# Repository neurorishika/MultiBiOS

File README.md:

# MultiBiOS: Precision Olfactometer Control System

<div align="center">

**High-precision, hardware-clocked olfactometer control system for behavioral neuroscience**

[📚 Documentation](https://neurorishika.github.io/MultiBiOS/) • [🚀 Quick Start](#quick-start) • [🔧 Installation](#installation) • [📖 Examples](#examples) • [🤝 Contributing](#contributing)

</div>

---

## 🧪 Overview

**MultiBiOS** (Multispecies Bilateral Odor delivery System) is a precision olfactometer control system designed for behavioral neuroscience experiments. It provides sub-millisecond timing control, complete experimental reproducibility, and comprehensive data logging.

### ✨ Key Features

- 🎯 **Sub-millisecond precision** with hardware-clocked timing via NI-DAQ
- 🔄 **Bilateral valve control** for complex comparative experiments  
- 📊 **Complete data provenance** with comprehensive logging and replay
- 🛡️ **Built-in safety guardrails** prevent timing conflicts at compile-time
- 🎲 **Reproducible randomization** via configurable random seeds
- 📈 **Interactive visualization** with real-time and post-hoc analysis
- ⏱️ **Real-time progress monitoring** shows expected protocol state during execution
- 🔌 **Teensy 4.1 firmware** for microsecond-precise valve preloading
- 📝 **YAML protocols** for human-readable experimental descriptions

### 🏗️ System Architecture

```
┌─────────────────┐    ┌─────────────────┐    ┌─────────────────┐
│   YAML Protocol │───▶│ Python Compiler │───▶│   NI-DAQ USB    │
│   Description   │    │   & Runner      │    │    6353         │
└─────────────────┘    └─────────────────┘    └─────────────────┘
                                                        │
                                                        ▼
                              ┌─────────────────────────────────────┐
                              │          Teensy 4.1 MCU             │
                              │    (Valve Pattern Preloading)      │
                              └─────────────────────────────────────┘
                                                │
                                                ▼
                              ┌─────────────────────────────────────┐
                              │       TPIC6B595 Shift Registers    │
                              │         (10MHz SPI Chain)          │
                              └─────────────────────────────────────┘
                                                │
                                                ▼
                              ┌─────────────────────────────────────┐
                              │      Olfactometer Valve Arrays     │
                              │    (8-valve bilateral control)     │
                              └─────────────────────────────────────┘
```

## 🚀 Quick Start

### Prerequisites

- Conda or Miniconda
- NI-DAQmx drivers (for hardware execution)
- Spinnaker SDK 4.3.0.189 installed on Windows before installing `PySpin`
- If you want live Blackfly input in FicTrac on this rig, build a Spinnaker-enabled FicTrac binary and configure the `fictrac` block in `config/hardware.yaml`

### Installation

```bash
# Clone the repository
git clone https://github.com/neurorishika/MultiBiOS.git
cd MultiBiOS

# Create the shared NI-DAQ + Blackfly camera environment
conda env create -f environment.yml
conda activate multibios-blackfly

# Verify the combined stack
python -c "import multibios, nidaqmx, PySpin; print('multibios-blackfly ready')"

# Optional app smoke tests
multibios-explorer --help
multibios-flow-monitor --help
```

This environment is intended to run both the MultiBiOS DAQ stack and the Blackfly camera scripts in one place. The rig camera model is **Teledyne FLIR Blackfly S BFS-U3-13Y3M**.

For live FicTrac on the Blackfly side camera, see `docs/fictrac.md`. MultiBiOS now prepares the Spinnaker runtime DLL path automatically before launching FicTrac, but you still need a FicTrac binary built with the upstream `PGR_USB3` option.

If you are on this workstation and want the same validated build that was used for the Blackfly side camera, run:

```powershell
cd C:\Rishika\MultiBiOS
.\tools\build_fictrac_spinnaker.ps1 -VcpkgRoot C:\Users\markd\vcpkg
```

The resulting binary is expected at `assets/fictrac-spinnaker/fictrac-spinnaker.exe`. The step-by-step build and usage guide lives in `docs/fictrac.md`.

FicTrac is treated as vendored source in this repo because MultiBiOS carries source-level patches in `assets/third_party/FicTrac`. The local build directory `assets/third_party/FicTrac-build` should remain untracked.

### Your First Protocol

1. **Preview a protocol** (no hardware required):
   ```bash
     python -m multibios.run_protocol \
      --yaml protocols/example_protocol.yaml \
       --hardware config/hardware.yaml \
       --dry-run --interactive
   ```

2. **Run on hardware** (requires NI-DAQ setup):
   ```bash
     python -m multibios.run_protocol \
      --yaml protocols/example_protocol.yaml \
       --hardware config/hardware.yaml
   ```

3. **Run with real-time progress monitoring**:
   ```bash
     python -m multibios.run_protocol \
      --yaml protocols/example_protocol.yaml \
       --hardware config/hardware.yaml \
       --verbose --progress
   ```
   
   This displays the expected protocol state during execution:
   ```
   DO Legend: [0:RCK] [1:LOAD_REQ] [2:S0] [3:S1] [4:S2]
   AO Legend: [0:MFC1] [1:MFC2]
   [  5%] 250.0ms | DO:░█░░█ | AO:0:2.50,1:1.20
   [ 10%] 500.0ms | DO:█░█░░ | AO:0:3.00,1:1.50
   ```
   (█=HIGH, ░=LOW, shows all channels at once!)

4. **Analyze results**:
   ```bash
  python -m multibios.viz_protocol data/runs/latest
   ```

## 📖 Examples

### Simple Bilateral Odor Delivery

```yaml
protocol:
  name: "Bilateral Odor Comparison"
  timing:
    sample_rate: 1000  # 1 kHz sampling
    seed: 42          # Reproducible randomization

sequence:
  - phase: "Baseline"
    duration: 30000   # 30 seconds
    times: 1
    actions:
      - device: "olfactometer.left"
        state: "AIR"
        timing: 0
      - device: "olfactometer.right"
        state: "AIR"
        timing: 0

  - phase: "Odor Presentation" 
    duration: 60000   # 1 minute per trial
    times: 5          # 5 trials
    randomize: true   # Randomize odor order
    actions:
      - device: "olfactometer.left"
        state: "ODOR1,ODOR2,ODOR3"  # Random selection
        timing: 10000               # 10s into trial
      - device: "triggers.microscope"
        state: true
        timing: 15000               # Trigger at 15s
```

### Advanced Multi-Device Coordination

```yaml
sequence:
  - phase: "Complex Trial"
    duration: 45000
    times: 10
    actions:
      # MFC setpoints
      - device: "mfc.air_left_setpoint"
        value: 2.1  # Volts
        timing: 0
      
      # Synchronized valve switching  
      - device: "olfactometer.left"
        state: "ODOR1"
        timing: 5000
      - device: "switch_valve.left"
        state: "ODOR" 
        timing: 5100  # 100ms later
        
      # Continuous camera triggers
      - device: "triggers.camera_continuous"
        state: true
        timing: 1000
      - device: "triggers.camera_continuous" 
        state: false
        timing: 40000
```

## 🔧 Hardware Setup

### Required Components

| Component | Description | Quantity |
|-----------|-------------|----------|
| **NI USB-6353** | Hardware-clocked DAQ | 1 |
| **Teensy 4.1** | Microcontroller for valve control | 1 |
| **TPIC6B595** | High-power shift registers | 4 |
| **Olfactometer valves** | Pneumatic valves (12V) | 8-16 |
| **Mass flow controllers** | Precision flow control | 2-4 |

### Wiring Overview

```
NI-DAQ ────┐
           ├─── LOAD_REQ (Hardware clock)
           ├─── S-bits (Device selection) 
           ├─── Analog I/O (MFC control)
           └─── Triggers (Microscope/Camera)

Teensy ────┐
           ├─── SPI Chain (10MHz)
           ├─── Interrupt handling
           └─── Safety interlocks

TPIC6B595 ─┼─── Valve Array Left
           ├─── Valve Array Right  
           ├─── Switch Valve Left
           └─── Switch Valve Right
```

📋 **[Complete wiring diagrams and setup instructions →](https://neurorishika.github.io/MultiBiOS/hardware/)**

## 📊 Data Output

MultiBiOS provides comprehensive data logging:

### Generated Files
```
data/runs/2025-08-21_14-07-33/
├── protocol_original.yaml      # Original protocol
├── protocol_compiled.yaml      # Compiled with timing  
├── hardware_config.yaml        # Hardware configuration
├── digital_output.npy          # DO timing arrays
├── analog_output.npy           # AO setpoints
├── analog_input.csv            # MFC feedback (if recorded)
├── timing_log.csv              # Execution timestamps
└── visualization.html          # Interactive plot
```

### Interactive Visualization

The system generates rich interactive plots showing:
- 📈 Commanded vs actual valve states
- 🎛️ Analog input/output traces  
- ⏱️ Timing precision analysis
- 🔍 Zoom and pan capabilities

## 🧪 Use Cases

MultiBiOS is designed for:

- **Behavioral choice experiments** with precise odor timing
- **Optogenetics** with synchronized light/odor delivery
- **Calcium imaging** with triggered acquisition
- **Electrophysiology** with sub-millisecond precision
- **Multi-animal** comparative studies
- **Reproducible protocols** across labs and sessions

## 🛡️ Safety & Reliability

### Built-in Safeguards
- ✅ **Compile-time validation** prevents hardware conflicts
- ✅ **Timing guardrails** ensure safe valve switching
- ✅ **State verification** with sticky S-bit monitoring  
- ✅ **Hardware interlocks** prevent damage
- ✅ **Complete logging** for audit trails

### Experimental Reproducibility
- 🎯 **Deterministic randomization** with configurable seeds
- 📝 **Complete parameter logging** 
- 🔄 **Protocol replay** capability
- 📊 **Timing validation** and verification
- 🏷️ **Version tracking** of all components

## 📚 Documentation

Comprehensive documentation is available at **[neurorishika.github.io/MultiBiOS](https://neurorishika.github.io/MultiBiOS/)**

### Quick Links
- 🏗️ [System Architecture](https://neurorishika.github.io/MultiBiOS/hardware/)
- 🔌 [Hardware Setup](https://neurorishika.github.io/MultiBiOS/wiring/) 
- 💾 [Firmware Guide](https://neurorishika.github.io/MultiBiOS/firmware/)
- 📝 [Protocol Reference](https://neurorishika.github.io/MultiBiOS/protocol/)
- 🏃 [Runner Application](https://neurorishika.github.io/MultiBiOS/runner/)
- 📈 [Visualization](https://neurorishika.github.io/MultiBiOS/visualization/)
- ❓ [FAQ](https://neurorishika.github.io/MultiBiOS/faq/)
- 🔧 [Troubleshooting](https://neurorishika.github.io/MultiBiOS/troubleshooting/)

## 🤝 Contributing

We welcome contributions! MultiBiOS is built for the neuroscience community.

### Ways to Contribute
- 🐛 **Report bugs** and request features
- 💡 **Submit improvements** to code or documentation  
- 🧪 **Share protocols** and use cases
- 🔧 **Hardware modifications** and extensions
- 📚 **Documentation** improvements

### Getting Started
```bash
# Fork the repository on GitHub
git clone https://github.com/yourusername/MultiBiOS.git
cd MultiBiOS

# Install development dependencies
poetry install --with dev

# Run tests
poetry run pytest

# Format code
poetry run black multibios/
poetry run ruff check multibios/
```

### Test And Tool Layout

- `tests/` is reserved for automated `pytest` coverage.
- `tools/manual_checks/` is for operator-facing hardware checks, probes, and bench scripts that are meant to be run directly.
- When adding new validation code, put reusable automated assertions under `tests/` and keep live camera, DAQ, MFC, or FicTrac helpers under `tools/manual_checks/`.

For a quick automated smoke pass from the repo root, run:

```bash
pytest tests/
```

📖 **[Full contributing guide →](https://neurorishika.github.io/MultiBiOS/contributing/)**

## 📄 License

This project is licensed under the MIT License - see the [LICENSE](LICENSE) file for details.

## 🙏 Acknowledgments

MultiBiOS was developed for the neuroscience research community. Special thanks to:
- The **Ruta and Kronauer Labs** for requirements and testing
- **National Instruments** for DAQ hardware support  
- The **Arduino/Teensy** community for firmware foundations
- **Open source contributors** who make science better

## 📞 Contact

- **Issues & Support:** [GitHub Issues](https://github.com/neurorishika/MultiBiOS/issues)
- **Email:** neurorishika@gmail.com  
- **Documentation:** [neurorishika.github.io/MultiBiOS](https://neurorishika.github.io/MultiBiOS/)

---

<div align="center">

**🧠 Built for Neuroscience • 🔬 Made with Science • 🚀 Open Source**

[⭐ Star this repo](https://github.com/neurorishika/MultiBiOS/stargazers) • [📖 Read the docs](https://neurorishika.github.io/MultiBiOS/) • [🤝 Contribute](CONTRIBUTING.md)

</div>

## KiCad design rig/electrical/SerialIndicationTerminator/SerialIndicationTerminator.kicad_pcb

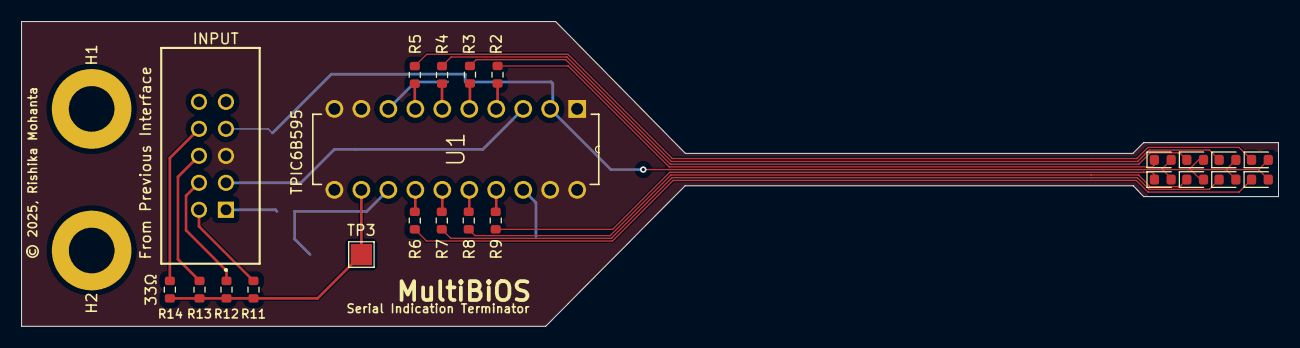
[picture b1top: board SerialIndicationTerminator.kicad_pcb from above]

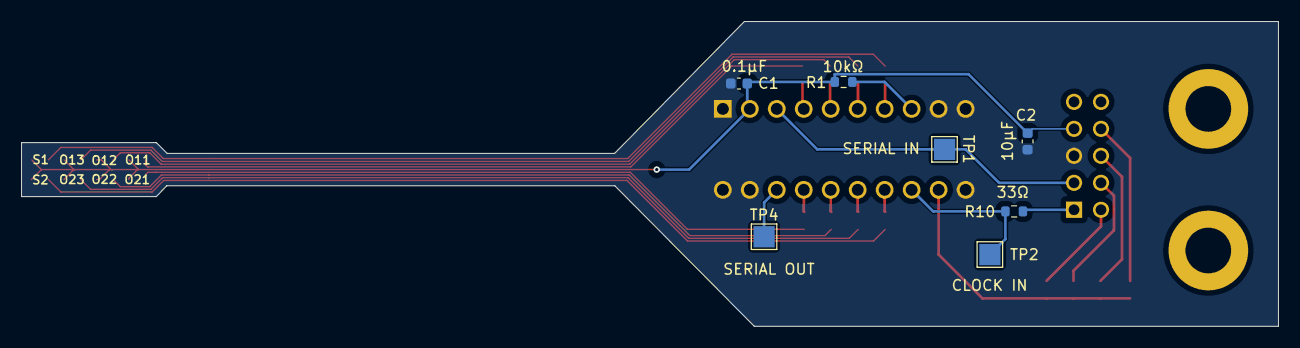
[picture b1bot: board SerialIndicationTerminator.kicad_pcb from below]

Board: 2 copper layers, 118.4 x 28.7 mm, 32 parts (7 on the bottom side), 28 nets.

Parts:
C1: 0.1u; C_0603_1608Metric
C2: 10uf; C_0603_1608Metric
D1, D2, D3, D4, D5, D6, D7, D8: LED; LED_0603_1608Metric
H1, H2: MountingHole; MountingHole_4.3mm_M4_DIN965_Pad
J1: TST-105-01-X-D; SAMTEC_TST-105-01-X-D
R1: 10k; R_0603_1608Metric
R2, R3, R4, R5, R6, R7, R8, R9: R; R_0603_1608Metric
R10, R11, R12, R13, R14: 33Ω; R_0603_1608Metric
TP1, TP2, TP3, TP4: TestPoint; TestPoint_Pad_2.0x2.0mm
U1: TPIC6595; DIP254P762X508-20

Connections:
+5V: C1.1, C2.1, D1.2 (A), D2.2 (A), D3.2 (A), D4.2 (A), D5.2 (A), D6.2 (A), D7.2 (A), D8.2 (A), J1.07, R1.2, U1.2 (VCC)
GND: C1.2, C2.2, J1.05, U1.1 (PGND), U1.9 (~G), U1.10 (PGND), U1.11 (PGND), U1.19 (LGND), U1.20 (PGND)
unnamed: D1.1 (K), R2.2
unnamed: D2.1 (K), R3.2
unnamed: D3.1 (K), R4.2
unnamed: D4.1 (K), R5.2
unnamed: D5.1 (K), R6.2
unnamed: D6.1 (K), R7.2
unnamed: D7.1 (K), R8.2
unnamed: D8.1 (K), R9.2
unnamed: J1.01, R10.1
unnamed: J1.02, R11.1
unnamed: J1.04, R12.1
unnamed: J1.06, R13.1
unnamed: J1.08, R14.1
unnamed: R2.1, U1.4 (DRAIN0)
unnamed: R3.1, U1.5 (DRAIN1)
unnamed: R4.1, U1.6 (DRAIN2)
unnamed: R5.1, U1.7 (DRAIN3)
unnamed: R6.1, U1.14 (DRAIN4)
unnamed: R7.1, U1.15 (DRAIN5)
unnamed: R8.1, U1.16 (DRAIN6)
unnamed: R9.1, U1.17 (DRAIN7)
unnamed: R11.2, R12.2, R13.2, R14.2, TP3.1, U1.12 (RCLK)
unnamed: J1.03, TP1.1, U1.3 (SER_IN)
unnamed: TP4.1, U1.18 (SER_OUT)
unnamed: R10.2, TP2.1, U1.13 (SRCK)
unnamed: R1.1, U1.8 (~SRCLR)

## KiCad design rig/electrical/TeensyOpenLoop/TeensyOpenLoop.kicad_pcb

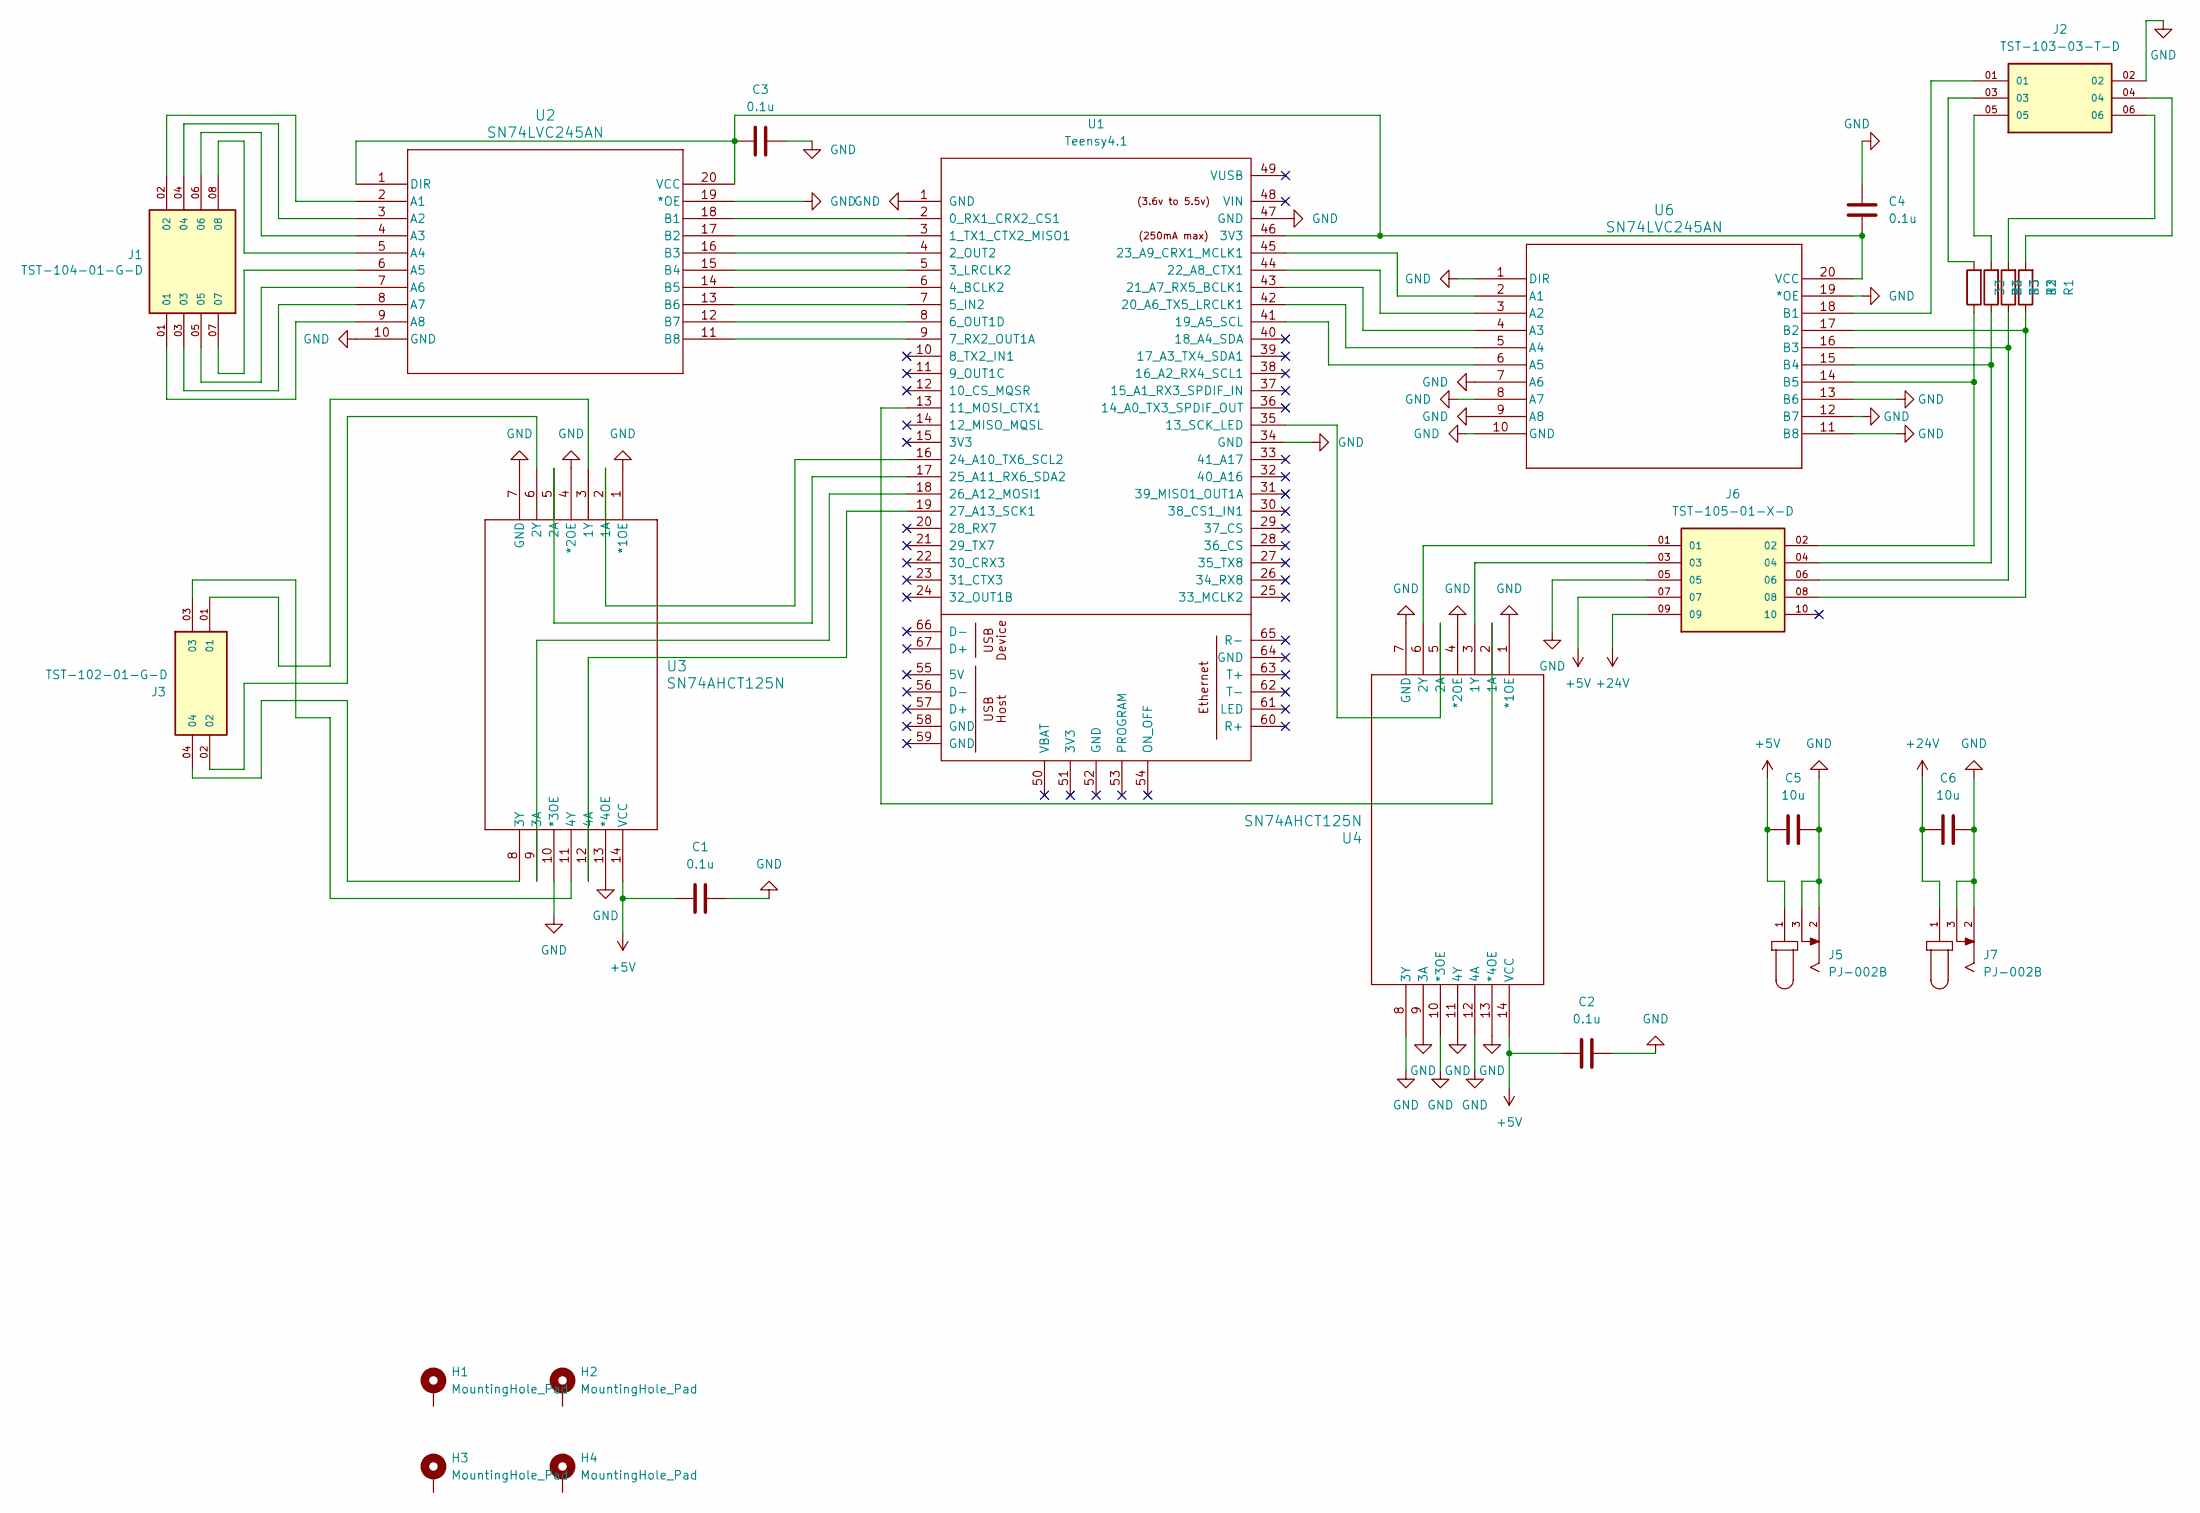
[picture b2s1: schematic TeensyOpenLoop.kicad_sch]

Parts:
C1, C2, C3, C4: 0.1u; C_0603_1608Metric
C5, C6: 10u; C_0603_1608Metric
H1, H2, H3, H4: MountingHole_Pad; MountingHole_3.2mm_M3_Pad
J1: TST-104-01-G-D; SAMTEC_TST-104-01-G-D; PARTREV R
J2: TST-103-03-T-D; SAMTEC_TST-103-03-T-D; PARTREV R
J3: TST-102-01-G-D; SAMTEC_TST-102-01-G-D; PARTREV R
J5, J7: PJ-002B; CUI_PJ-002B
J6: TST-105-01-X-D; SAMTEC_TST-105-01-X-D; PARTREV 1-23-96
R1, R2, R3, R4: 33; R_Axial_DIN0207_L6.3mm_D2.5mm_P10.16mm_Horizontal
U1: Teensy4.1; Teensy41
U2, U6: SN74LVC245AN; N20
U3, U4: SN74AHCT125N; N14

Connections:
+5V: C1.1, C2.1, C5.1, J5.1, J6.07, U3.14 (VCC), U4.14 (VCC)
+24V: C6.1, J6.09, J7.1
GND: C1.2, C2.2, C3.2, C4.1, C5.2, C6.2, J2.02, J5.2, J5.3, J6.05, J7.2, J7.3, U1.1 (GND), U1.34 (GND), U1.47 (GND), U2.10 (GND), U2.19 (*OE), U3.1 (*1OE), U3.4 (*2OE), U3.7 (GND), U3.10 (*3OE), U3.13 (*4OE), U4.1 (*1OE), U4.4 (*2OE), U4.7 (GND), U4.8 (3Y), U4.9 (3A), U4.10 (*3OE), U4.11 (4Y), U4.12 (4A), U4.13 (*4OE), U6.1 (DIR), U6.7 (A6), U6.8 (A7), U6.9 (A8), U6.10 (GND), U6.11 (B8), U6.12 (B7), U6.13 (B6), U6.19 (*OE)
unnamed: J2.03, R4.2
unnamed: J2.04, R1.2
unnamed: J2.05, R3.2
unnamed: J2.06, R2.2
unnamed: U1.2 (0_RX1_CRX2_CS1), U2.18 (B1)
unnamed: U1.3 (1_TX1_CTX2_MISO1), U2.17 (B2)
unnamed: U1.4 (2_OUT2), U2.16 (B3)
unnamed: U1.5 (3_LRCLK2), U2.15 (B4)
unnamed: U1.6 (4_BCLK2), U2.14 (B5)
unnamed: U1.7 (5_IN2), U2.13 (B6)
unnamed: U1.8 (6_OUT1D), U2.12 (B7)
unnamed: U1.9 (7_RX2_OUT1A), U2.11 (B8)
unnamed: U1.13 (11_MOSI_CTX1), U4.2 (1A)
unnamed: U1.35 (13_SCK_LED), U4.5 (2A)
unnamed: U1.41 (19_A5_SCL), U6.6 (A5)
unnamed: U1.42 (20_A6_TX5_LRCLK1), U6.5 (A4)
unnamed: U1.43 (21_A7_RX5_BCLK1), U6.4 (A3)
unnamed: U1.44 (22_A8_CTX1), U6.3 (A2)
unnamed: U1.45 (23_A9_CRX1_MCLK1), U6.2 (A1)
unnamed: U1.16 (24_A10_TX6_SCL2), U3.2 (1A)
unnamed: U1.17 (25_A11_RX6_SDA2), U3.5 (2A)
unnamed: U1.18 (26_A12_MOSI1), U3.9 (3A)
unnamed: U1.19 (27_A13_SCK1), U3.12 (4A)
unnamed: J1.02, U2.2 (A1)
unnamed: J1.04, U2.3 (A2)
unnamed: J1.06, U2.4 (A3)
unnamed: J1.08, U2.5 (A4)
unnamed: J1.07, U2.6 (A5)
unnamed: J1.05, U2.7 (A6)
unnamed: J1.03, U2.8 (A7)
unnamed: J1.01, U2.9 (A8)
unnamed: C3.1, C4.2, U1.46 (3V3), U2.1 (DIR), U2.20 (VCC), U6.20 (VCC)
unnamed: J3.01, U3.3 (1Y)
unnamed: J3.02, U3.6 (2Y)
unnamed: J3.04, U3.8 (3Y)
unnamed: J3.03, U3.11 (4Y)
unnamed: J6.03, U4.3 (1Y)
unnamed: J6.01, U4.6 (2Y)
unnamed: J2.01, U6.18 (B1)
unnamed: J6.08, R1.1, U6.17 (B2)
unnamed: J6.06, R2.1, U6.16 (B3)
unnamed: J6.04, R3.1, U6.15 (B4)
unnamed: J6.02, R4.1, U6.14 (B5)

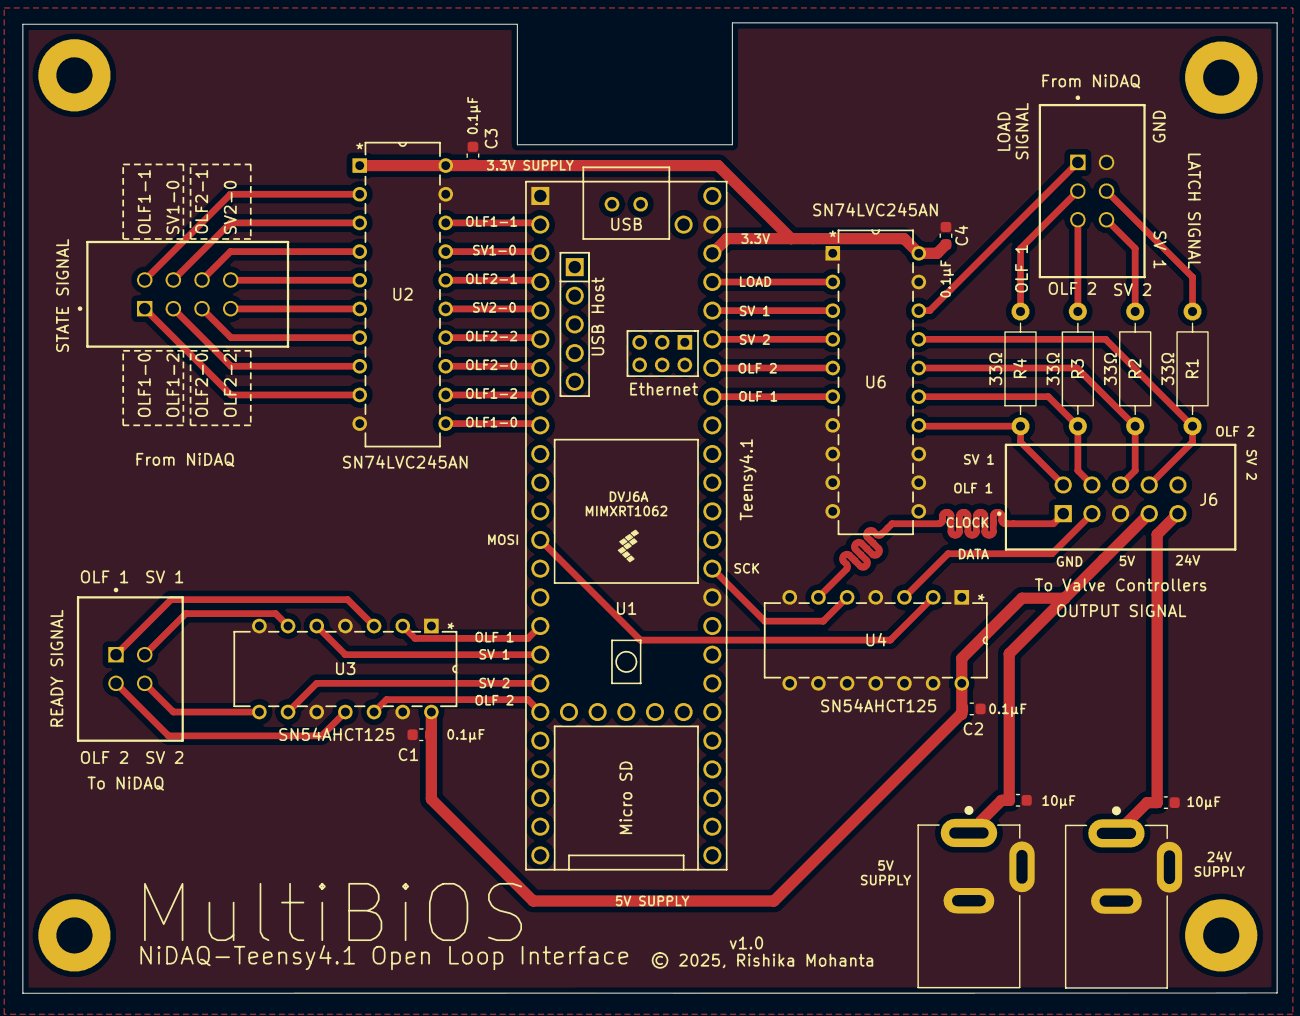
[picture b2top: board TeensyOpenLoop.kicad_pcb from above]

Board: 2 copper layers, 111.1 x 86.0 mm, 25 parts (0 on the bottom side), 46 nets.

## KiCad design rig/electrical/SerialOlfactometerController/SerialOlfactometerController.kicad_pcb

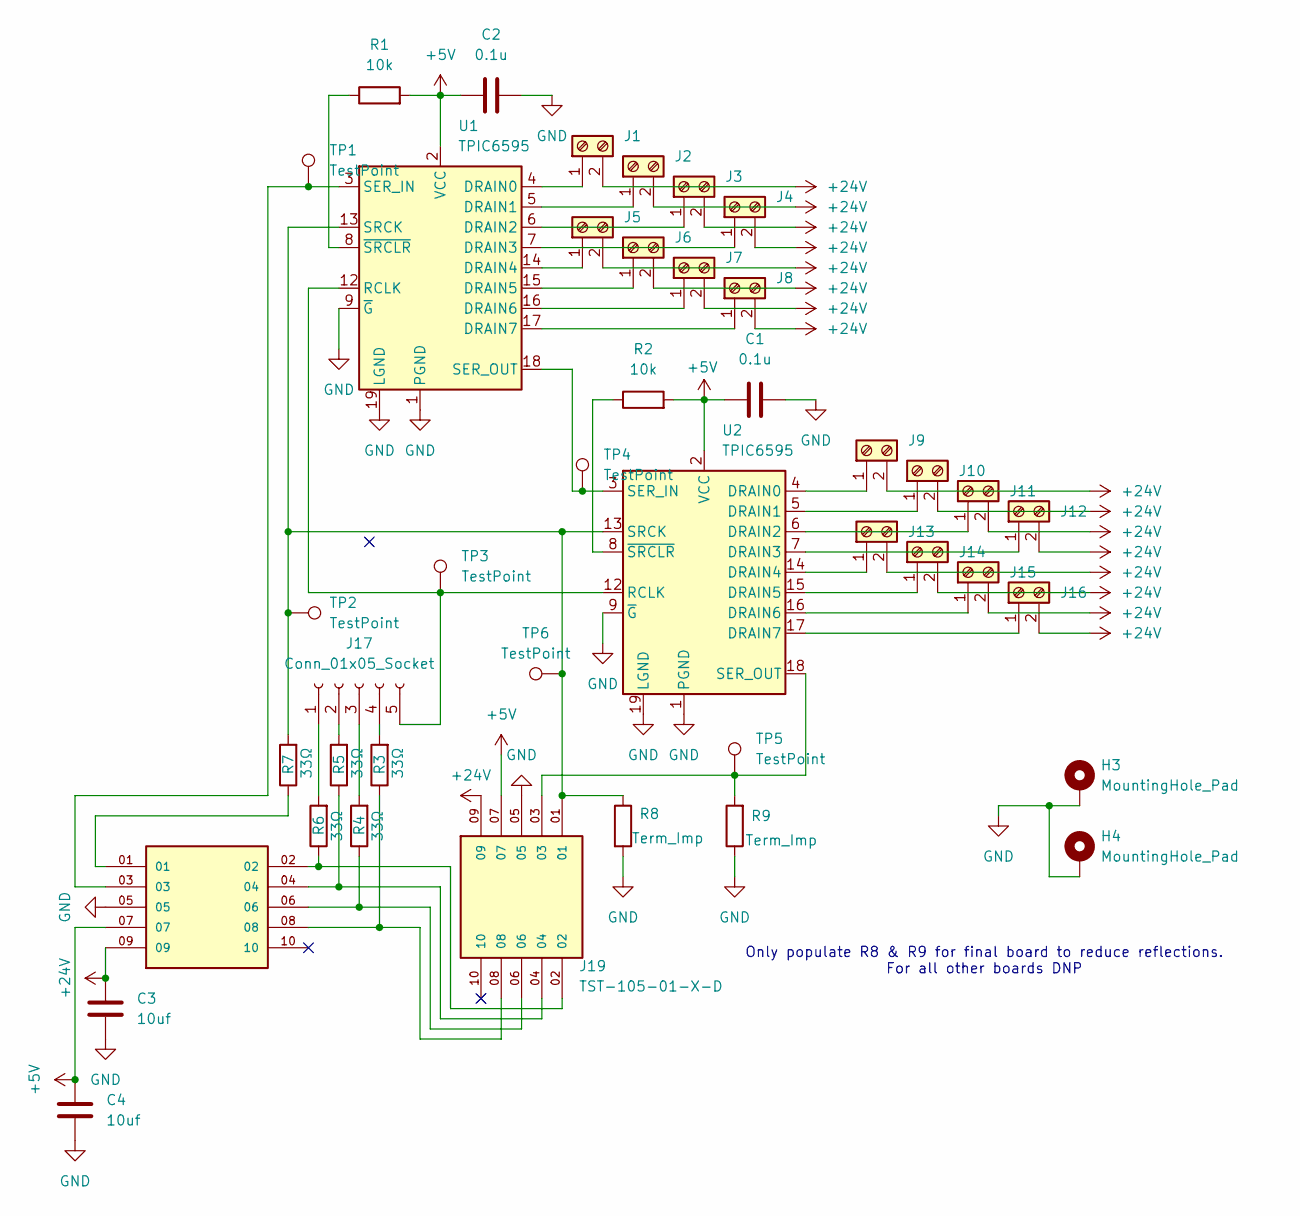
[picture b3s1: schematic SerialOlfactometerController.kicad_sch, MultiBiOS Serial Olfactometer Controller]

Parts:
C1, C2: 0.1u; C_0603_1608Metric
C3, C4: 10uf; C_0603_1608Metric
H3, H4: MountingHole_Pad; MountingHole_3.2mm_M3_Pad
J1, J2, J3, J4, J5, J6, J7, J8, J9, J10, J11, J12, J13, J14, J15, J16: Screw_Terminal_01x02; PHOENIX_1935310
J17: Conn_01x05_Socket; PinSocket_1x05_P2.54mm_Vertical
J18, J19: TST-105-01-X-D; SAMTEC_TST-105-01-X-D; PARTREV 1-23-96
R1, R2: 10k; R_0603_1608Metric
R3, R4, R5, R6, R7: 33Ω; R_0603_1608Metric
R8, R9: Term_Imp; R_0603_1608Metric
TP1, TP2, TP3, TP4, TP5, TP6: TestPoint; TestPoint_Pad_2.0x2.0mm
U1, U2: TPIC6595; DIP254P762X508-20

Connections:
+5V: C1.1, C2.1, C4.1, J18.07, J19.07, R1.2, R2.2, U1.2 (VCC), U2.2 (VCC)
+24V: C3.1, J1.2, J2.2, J3.2, J4.2, J5.2, J6.2, J7.2, J8.2, J9.2, J10.2, J11.2, J12.2, J13.2, J14.2, J15.2, J16.2, J18.09, J19.09
GND: C1.2, C2.2, C3.2, C4.2, H3.1, H4.1, J18.05, J19.05, R8.2, R9.1, U1.1 (PGND), U1.9 (~G), U1.10 (PGND), U1.11 (PGND), U1.19 (LGND), U1.20 (PGND), U2.1 (PGND), U2.9 (~G), U2.10 (PGND), U2.11 (PGND), U2.19 (LGND), U2.20 (PGND)
unnamed: J1.1, U1.4 (DRAIN0)
unnamed: J2.1, U1.5 (DRAIN1)
unnamed: J3.1, U1.6 (DRAIN2)
unnamed: J4.1, U1.7 (DRAIN3)
unnamed: J5.1, U1.14 (DRAIN4)
unnamed: J6.1, U1.15 (DRAIN5)
unnamed: J7.1, U1.16 (DRAIN6)
unnamed: J8.1, U1.17 (DRAIN7)
unnamed: J9.1, U2.4 (DRAIN0)
unnamed: J10.1, U2.5 (DRAIN1)
unnamed: J11.1, U2.6 (DRAIN2)
unnamed: J12.1, U2.7 (DRAIN3)
unnamed: J13.1, U2.14 (DRAIN4)
unnamed: J14.1, U2.15 (DRAIN5)
unnamed: J15.1, U2.16 (DRAIN6)
unnamed: J16.1, U2.17 (DRAIN7)
unnamed: J17.1, R6.2
unnamed: J17.2, R5.2
unnamed: J17.3, R4.2
unnamed: J17.4, R3.2
unnamed: J17.5, TP3.1, U1.12 (RCLK), U2.12 (RCLK)
unnamed: J18.01, R7.1
unnamed: J18.02, J19.02, R6.1
unnamed: J18.04, J19.04, R5.1
unnamed: J18.06, J19.06, R4.1
unnamed: J18.08, J19.08, R3.1
unnamed: J18.03, TP1.1, U1.3 (SER_IN)
unnamed: TP4.1, U1.18 (SER_OUT), U2.3 (SER_IN)
unnamed: J19.01, R7.2, R8.1, TP2.1, TP6.1, U1.13 (SRCK), U2.13 (SRCK)
unnamed: R1.1, U1.8 (~SRCLR)
unnamed: J19.03, R9.2, TP5.1, U2.18 (SER_OUT)
unnamed: R2.1, U2.8 (~SRCLR)

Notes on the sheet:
Only populate R8 & R9 for final board to reduce reflections. For all other boards DNP

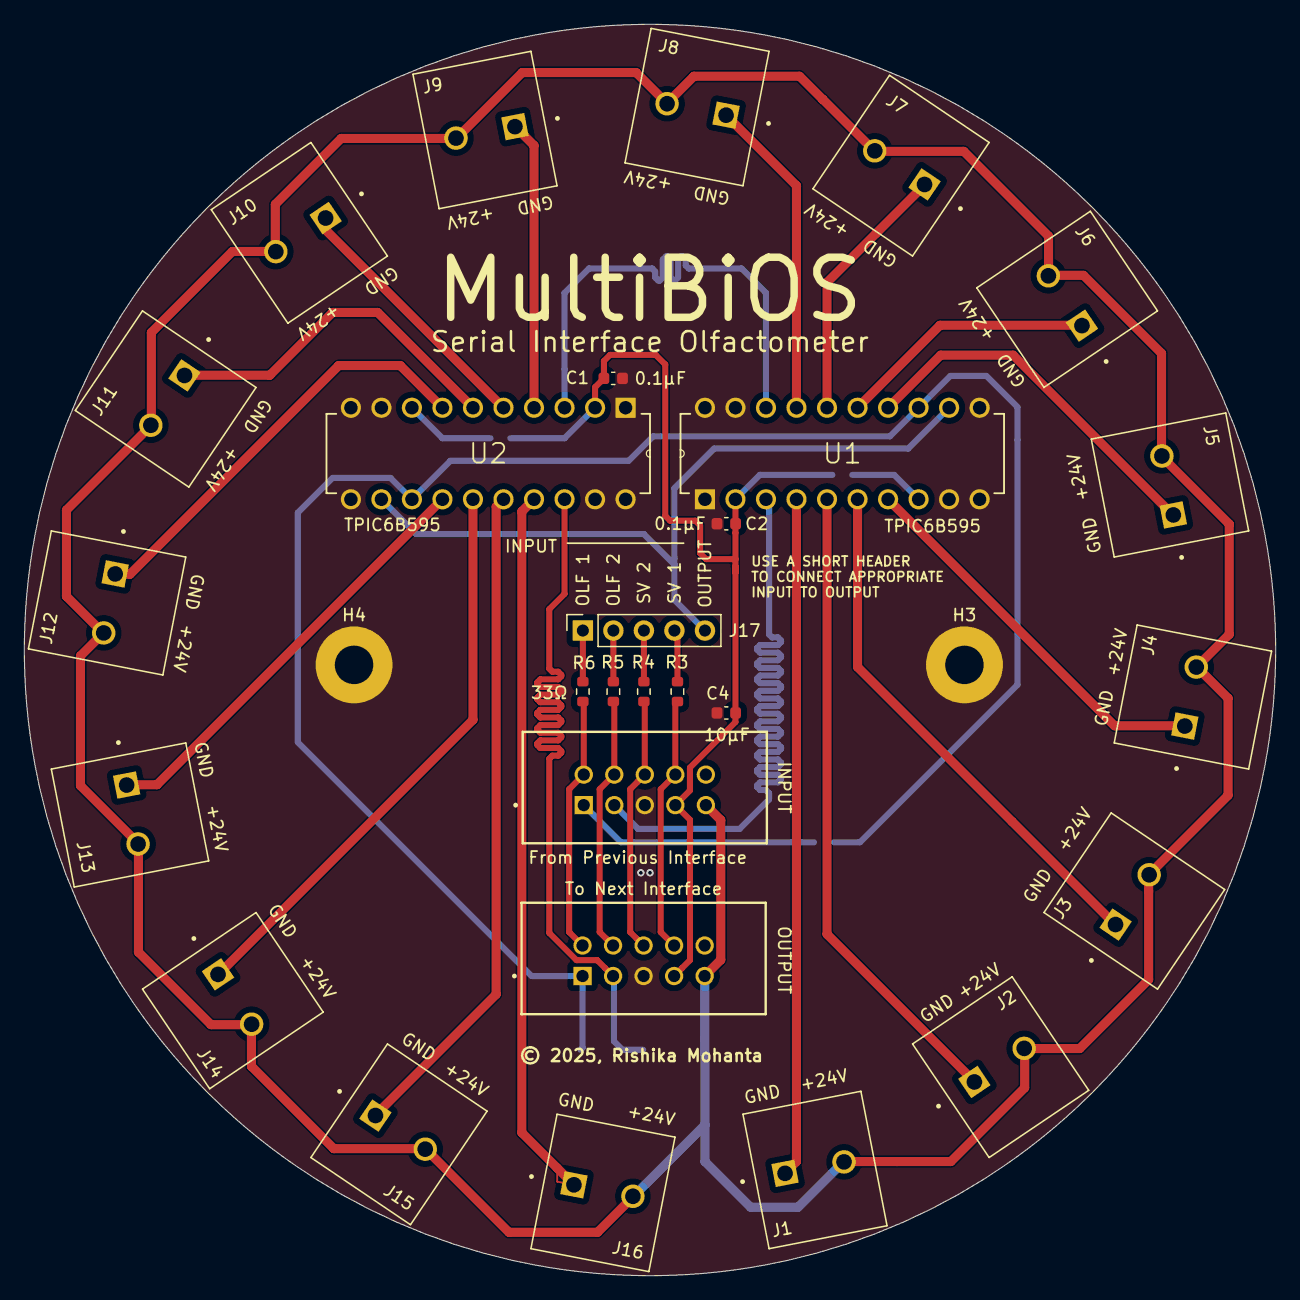
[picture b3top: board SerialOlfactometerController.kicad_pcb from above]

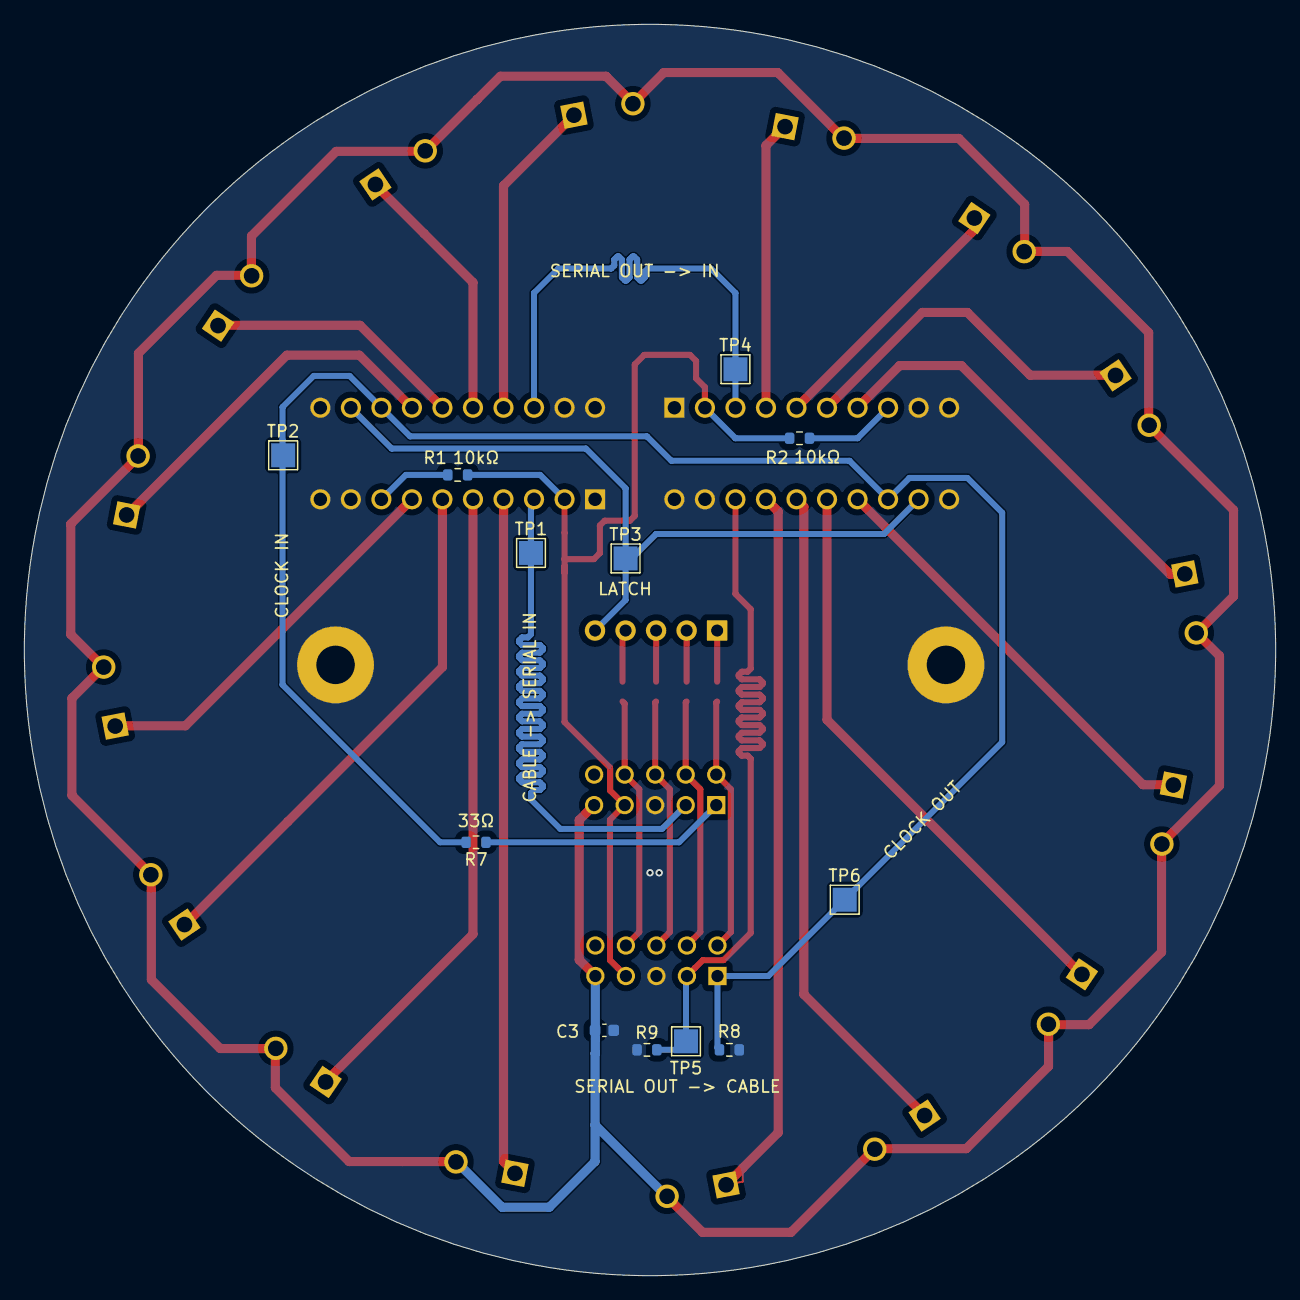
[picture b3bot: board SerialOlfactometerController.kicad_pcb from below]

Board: 2 copper layers, 104.1 x 104.1 mm, 42 parts (12 on the bottom side), 35 nets.

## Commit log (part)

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2025-08-21 Add initial project structure and dependencies for Multibios
    - Created `run_protocol.py` and `viz_protocol.py` files.
    - Initialized `poetry.lock` with dependencies.
    - Added `pyproject.toml` with project metadata and dependencies including mkinit and lazy-loader.
2025-08-21 Remove unused VSCode configuration and add .gitignore and .gitkeep files for project structure
2025-08-21 Update Python version requirement and add new dependencies
    - Changed the Python version requirement to >=3.11,<3.13.
    - Added new dependencies: numpy, pyyaml, nidaqmx, and matplotlib with specified version ranges.
    -added the run protocol and viz protocol
2025-08-21 Add comprehensive documentation for MultiBiOS system
    - Introduced FAQ section covering system architecture, timing, performance, hardware setup, protocol development, troubleshooting, data analysis, contributing, and support.
    - Documented Teensy 4.1 firmware details including state coding and communication protocols.
    - Detailed hardware architecture and signal naming conventions for the system.
    - Created an overview of the MultiBiOS system, highlighting key features and quick start instructions.
    - Explained logging and artifacts generated during protocol runs.
    - Specified YAML protocol structure and timing configuration details.
2025-08-21 Add initial README.md with project overview, features, and installation instructions
2025-08-21 Deployed c07407f with MkDocs version: 1.6.1
2025-08-21 Add mkdocs directory to .gitignore
2025-08-21 Update documentation and code references to replace NI USB-6363 with NI USB-6353
2025-08-22 Deployed a7153de with MkDocs version: 1.6.1
2025-08-27 Refactor protocol configuration and compilation logic
    - Updated the odor presentation protocol in `example_protocol.yaml` to set `randomize` to false for the odor presentation trial.
    - Enhanced the `ProtocolCompiler` class in `schema.py` with stricter state validation and improved type safety using `Literal` for state names.
    - Implemented detailed logging of compilation reports, including timing and state transitions.
    - Added functionality to generate a comprehensive JSON report of the compiled protocol in `run_protocol.py`.
2025-08-28 Add GLOBAL_LOAD_REQ support and enhance device grouping in visualization
    - Implemented GLOBAL_LOAD_REQ signal handling in run_protocol.py and viz_protocol.py, allowing for better signal management and visualization.
    - Updated color coding for GLOBAL_LOAD_REQ to improve clarity in interactive figures.
    - Enhanced device grouping logic to include a new "Global" category for better organization in plots.
    - Adjusted setup_hold_samples default value in main function to 5 for improved timing consistency.
    - Introduced new Teensy 4.1 firmware (v1_global_load.ino) to manage GLOBAL_LOAD_REQ with independent RCK latches and a 48-bit data chain.
    - Established a clear wiring summary and logical model for
2025-09-16 Refactor visualization and protocol handling
    - Moved figure creation logic from `viz_protocol.py` to a new helper module `viz_helpers.py` for better code organization and reusability.
    - Introduced `load_run_artifacts` function to streamline loading of run data and metadata.
    - Updated `make_protocol_figure` to handle digital outputs (DO), analog outputs (AO), and optional analog inputs (AI) and digital inputs (DI) with improved color grouping and layout.
    - Added a new configuration file `short_protocol.yaml` for defining odor presentation protocols with detailed timing and action sequences.
    - Cleaned up the main function in `viz_protocol.py` to utilize the new helper functions and improve rea
2025-09-16 Update data type handling in DigitalMultiChannelWriter and AnalogMultiChannelWriter
2025-09-16 feat(tests): Add comprehensive hardware testing utilities and examples
    - Implemented `hardware_test.py` for generating synchronized square waves on digital and analog outputs, including input monitoring and logging.
    - Created `simple_test.py` for continuous square wave generation on specified lines.
    - Added detailed README documentation for the hardware test script, outlining usage, command line options, and troubleshooting steps.
    - Introduced example scripts (`quick_test_examples.ps1` and `quick_test_examples.sh`) for quick hardware testing scenarios.
    - Updated `viz_helpers.py` to correct hovertemplate formatting for visualization.
2025-09-25 Add MultiBiOS Teensy 4.1 firmware with SD card logging
    - Implemented global command loading and latching for dual olfactometer and switch system.
    - Added non-blocking SD card logging for command loads and latch events.
    - Defined pin configurations for SPI communication, control signals, and status outputs.
    - Created a circular buffer for log messages to manage SD card writes efficiently.
    - Enhanced interrupt service routines (ISRs) for handling global load requests and RCK signals.
    - Included initialization routines for SD card and SPI setup, ensuring robust error handling.
2025-09-25 Added PCBs to repository
2025-09-25 Refactor code structure for improved readability and maintainability
2025-09-26 Serial Olfactometer improved design
2025-09-30 valve updated
2025-10-01 Tweaking of v1 boards
2025-10-02 Termination Resistors/GND Vias
    Added termination resistors to avoid reflections on signal lines. Added vias to GND plane stubs to avoid antennae effects.
2025-10-02 Add SerialValveController BOM and update Olfactometer BOM
    Added ibom.html for SerialValveController and updated ibom.html for SerialOlfactometerController. These changes provide updated interactive BOMs for both controllers.
2025-11-12 updates to electrical
2025-11-13 fixed firmware
2026-02-27 Add Teensy 4.1 firmware for TPIC6B595 controller and walking test
    - Implemented a serial-staged controller for TPIC6B595 with commands for ON/OFF/TOGGLE, SEND, PRINT, CLEAR, RESET, and macros for olfactometers and switches.
    - Added a walking test script to sequentially activate allowed bits with specified timing.
    - Introduced a continuous latcher tester script to send latch signals for hardware responsiveness testing.
    - Created initial test structure with __init__.py for test organization.
2026-03-12 Add TeensyController for thread-safe serial communication with Teensy v2
    - Implemented a high-level interface for controlling olfactometers and switch valves.
    - Added methods for setting olfactometer states (OFF, AIR, ODOR1-ODOR5, FLUSH) and switch valve states (CLEAN, ODOR).
    - Included command tagging for reliable response matching and ensured thread safety with a locking mechanism.
    - Established connection lifecycle management with open and close methods.
    - Provided a status method to retrieve the full status dump from the Teensy.
2026-03-21 Add comprehensive documentation for running experiments and timing synchronization analysis
    - Created `running_experiments.md` to guide users through the setup, execution, and verification of olfactometer experiments with MultiBiOS.
    - Introduced a detailed hardware checklist, software setup instructions, and step-by-step protocols for running experiments.
    - Added a section on common problems and quick reference commands for ease of use.
    - Established `timing_synchronization_analysis.md` to outline strategies for achieving precise timing synchronization across various components in the experimental setup.
    - Discussed current architecture, main timing problems, and provided recommendations for
2026-05-03 Update FicTrac packaging and submodule
2026-05-03 Update FicTrac submodule to hardening branch
2026-05-03 remove tmp folder from git tracking
2026-05-11 Add dual mode controller firmware and run paths configuration
    - Implemented dual_mode_controller.ino for Teensy 4.1, enabling open-loop and serial modes with SPI communication.
    - Introduced run_paths.py to resolve output paths based on hardware configuration.
    - Created tests for run_paths to ensure correct resolution of output directories and integration with parity and FicTrac audits.
    - Added hardware.yaml configuration file for device settings, including digital and analog inputs/outputs, and data output paths.
2026-06-02 Refactor odor lateralization protocol flow rate and update test configurations
    - Increased the MFC odor flow rate from 0.03 to 0.3 in the odor lateralization protocol YAML.
    - Enhanced the test for experiment FicTrac callback to include additional camera configuration fields and validation for hardware owned fields.
    - Added tests to validate imaging dataset requirements for completed microscopy runs and ensure proper handling of imaging acquisition details.
    - Introduced numeric expression evaluation for protocol timing expressions to allow dynamic calculations within the protocol.
    - Created a new script for sending two microscope trigger pulses with configurable parameters.
    - Updated hardware
2026-06-02 Enhance metadata form with microscopy start confirmation and update experiment record structure
2026-06-02 Refactor imaging dataset handling and metadata history logging
    - Enhanced the `find_runs` and `load_run` functions to read protocol names from both the visible run-root copy and the canonical inputs snapshot for backward compatibility.
    - Updated the metadata form to include new fields for acquired iterations, channels, and planes, and adjusted the logic to infer these values from the selected imaging dataset.
    - Introduced CSV logging for metadata history, allowing for appending entries and deriving history from CSV logs.
    - Implemented a new directory selection dialog for Windows using PowerShell for better user experience.
    - Added tests for new functionality, including metadata inference fro
2026-06-02 Enhance metadata history persistence to support CSV format and improve type handling for history CSV fields

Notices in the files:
README.md:
License: MIT
rig/electrical/SerialIndicationTerminator/SerialIndicationTerminator.kicad_pcb:
© 2025, Rishika Mohanta
